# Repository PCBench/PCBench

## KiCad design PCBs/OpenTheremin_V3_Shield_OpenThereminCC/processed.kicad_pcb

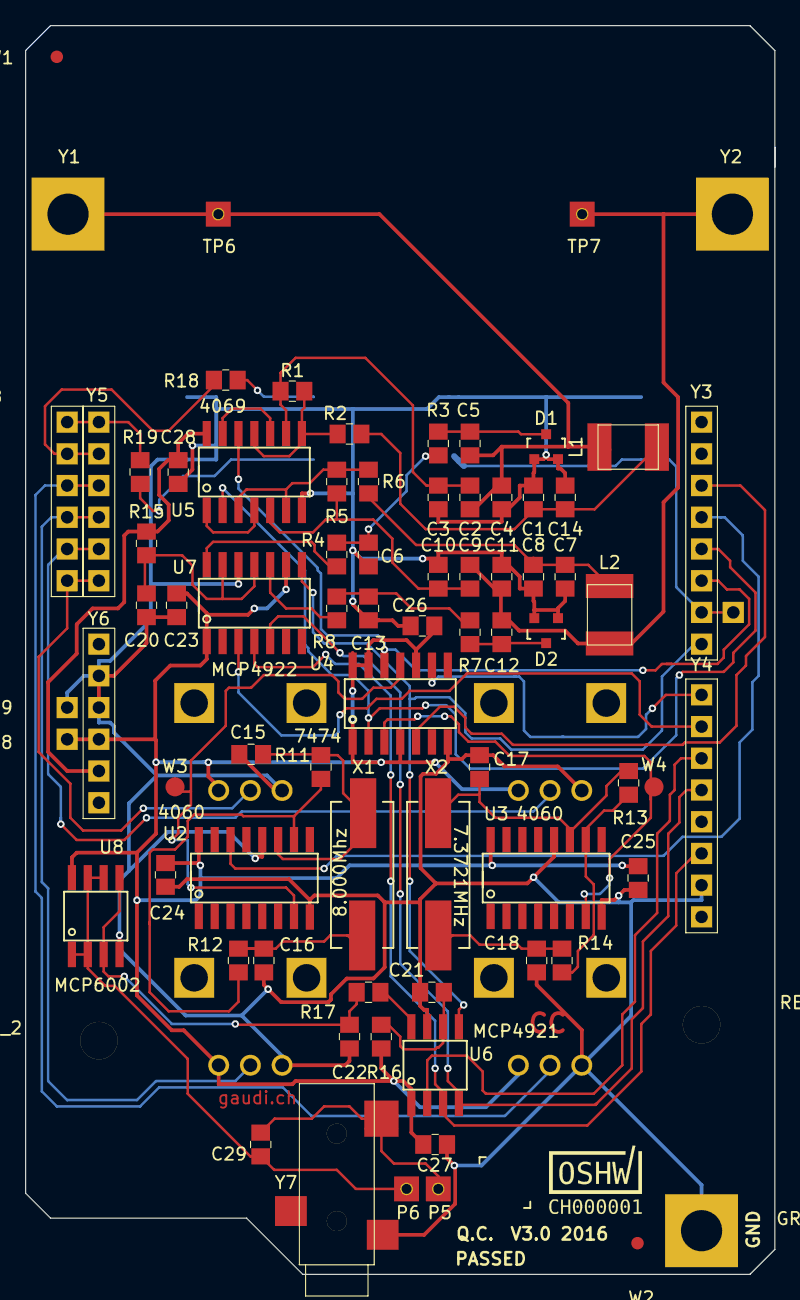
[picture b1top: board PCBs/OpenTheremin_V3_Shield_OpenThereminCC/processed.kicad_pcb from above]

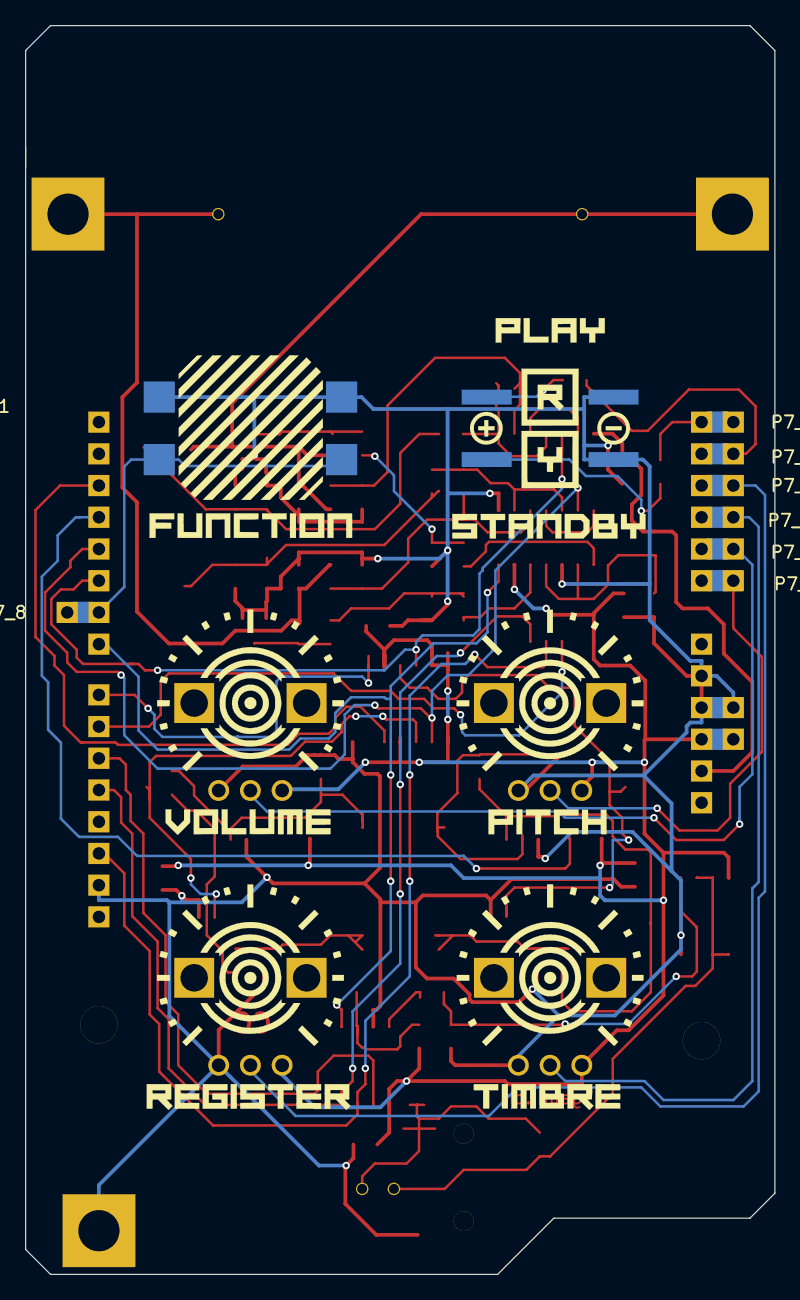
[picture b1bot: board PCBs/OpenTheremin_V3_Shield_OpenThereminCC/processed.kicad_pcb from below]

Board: 2 copper layers, 60.0 x 100.0 mm, 95 parts (17 on the bottom side), 52 nets.

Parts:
C1: 220pF 270pF?; 0805G
C2, C3, C9, C10: 150pF; 0805G
C4: 15nF?; 0805G
C5, C12: 470pF; 0805G
C6, C13, C23, C24, C25, C26, C27, C28: 100nF; 0805G
C7, C14: ?pF; 0805G
C8: 330pF; 0805G
C11: 0; 0805G
C15, C16, C17, C18: 33pF; 0805G
C20, C21: 100n; 0805G
C22: 10n; 0805G
C29: 10uF; 0805G
D1, D2: BB914; SOT-23
D3, D4: LED; LED_SQUARE_5mm
GROUND1: GND_PAD; MountPad3
L1, L2: 1mH; COIL
P1, P2, P3, P4: 10k; POT
P5: SP+; MeasurePad_Square_wHole_2mm
P6: SP-; MeasurePad_Square_wHole_2mm
P7, P7_2, P7_3, P7_4, P7_5, P7_6, P7_7, P7_8, P7_10: CONN_01X01; SMD_Pinheader_1_OT_BLANK
P7_9, P8, P9: CONN_01X01; SMD_Pinheader_1_OT
R1, R5, R11, R13: 4.7M; 0805G
R2, R6, R17: 2.2k; 0805G
R3, R4, R7, R8, R15, R16: 100k; 0805G
R12, R14, R18, R19: 470; 0805G
SW1: SW_PUSH; PUSH_BUTTON_TL3300D
TP6: PITCH ANTENNA; MeasurePad_Square_wHole_2mm
TP7: VOLUME ANTENNA; MeasurePad_Square_wHole_2mm
U1: Arduino_UNO_R2; ArduinoUNO
U2, U3: 4060; SOIC-16_N
U4: 74HC74; SOIC-14_N
U5: 4069; SOIC-14_N
U6: MCP4921-E/SN; SOIC-08_N
U7: MCP4922-E/SL; SOIC-14_N
U8: LM358 / MCP6002; SOIC-08_N
W1: FIDUCIAL1; Fiducial_1mm_Dia_2.54mm_Outer_CopperTop
W2: FIDUCIAL2; Fiducial_1mm_Dia_2.54mm_Outer_CopperTop
W3: TP1; Measurement_Point_Round-SMD-Pad_Small
W4: TP2; Measurement_Point_Round-SMD-Pad_Small
X1: 8MHz; Crystal_HC49-SD_SMD
X2: 7.3721MHz; Crystal_HC49-SD_SMD
Y1, Y2: MountPad3
Y3, Y4: CONN_01X08; SMD_Pinheader_8_OT
Y5, Y6, Y8: CONN_01X06; SMD_Pinheader_6_OT
Y7: PLUG_3_5_SMD; PLUG3_5_SwitchCraft_2B

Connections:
A0: P1.2, Y5.6, Y8.6
A1: P2.2, Y5.5, Y8.5
A2: P3.2, Y5.4, Y8.4
A3: P4.2, Y5.3, Y8.3
BUT: P7_9.1, SW1.1, Y3.7
DAC2_CS: U7.3, Y4.2
DAC_CS: U6.2, Y4.3
DAC_DI: U6.4, U7.5, Y4.4
DAC_LATCH: U6.5, U7.8, Y3.8
DAC_SCK: U6.3, U7.4, Y4.6
F_PITCH: U4.9, Y4.1
F_VOL: U4.5, Y3.3
GND: C1.2, C3.2, C4.2, C6.2, C7.2, C8.2, C10.2, C11.2, C13.2, C14.2, C15.2, C16.2, C17.2, C18.2, C20.2, C21.2, C22.2, C23.2, C24.2, C25.2, C26.2, C27.2, C28.2, D1.1, D1.2, D2.1, D2.2, D3.1, D4.1, GROUND1.1, P1.1, P2.1, P3.1, P4.1, P9.1, SW1.2, U2.8, U2.12, U3.8, U3.12, U4.7, U5.7, U6.7, U7.12, U8.4, Y4.7, Y6.2, Y6.3, Y7.1
LED_GREEN: R18.2, Y5.2, Y8.2
LED_RED: R19.2, Y5.1, Y8.1
unnamed: C1.1, C14.1, L1.2, R2.1
unnamed: C2.1, C4.1, C5.1, L1.1, TP6.1, Y1.1
unnamed: C2.2, C3.1, R1.2, U5.9
unnamed: C5.2, D1.3, R3.2
unnamed: C6.1, R3.1, R4.1
unnamed: C7.1, C8.1, L2.2, R6.1
unnamed: C9.2, C10.1, R5.2, U5.5
unnamed: C9.1, C11.1, C12.1, L2.1, TP7.1, Y2.1
unnamed: C12.2, D2.3, R7.2
unnamed: C13.1, R7.1, R8.1
unnamed: C15.1, R11.2, U2.11, X1.1
unnamed: C16.1, R12.1, X1.2
unnamed: C17.1, R13.2, U3.11, X2.1
unnamed: C18.1, R14.1, X2.2
unnamed: C21.1, R16.1, U6.6
unnamed: C22.1, R17.2, U8.3, U8.5
unnamed: C29.1, P6.1, U8.1, U8.2, U8.6, U8.7
unnamed: C29.2, P5.1, Y7.3
unnamed: D3.2, R18.1
unnamed: D4.2, R19.1
unnamed: R1.1, R2.2, U5.8, U5.11
unnamed: R4.2, U7.14
unnamed: R5.1, R6.2, U5.3, U5.6
unnamed: R11.1, R12.2, U2.10
unnamed: R13.1, R14.2, U3.10
unnamed: R17.1, U6.8
unnamed: U2.7, U4.11, W3.1
unnamed: U3.7, U4.3, W4.1
unnamed: U5.1, U5.4
unnamed: U5.10, U5.13
SAMPLE_CLK: U2.14, Y3.4
VCC: C23.1, C24.1, C25.1, C26.1, C27.1, P1.3, P2.3, P3.3, P4.3, P8.1, R16.2, U2.16, U3.16, U4.1, U4.4, U4.10, U4.13, U4.14, U6.1, U7.1, U7.9, U8.8, Y6.4
VDD: C28.1, R15.2, U5.14, Y6.5
VO_PITCH: U4.12, U5.12, Y3.6
VO_VOL: U4.2, U5.2, Y3.5
VoutB: R8.2, U7.10
VrefB: C20.1, R15.1, U7.11, U7.13

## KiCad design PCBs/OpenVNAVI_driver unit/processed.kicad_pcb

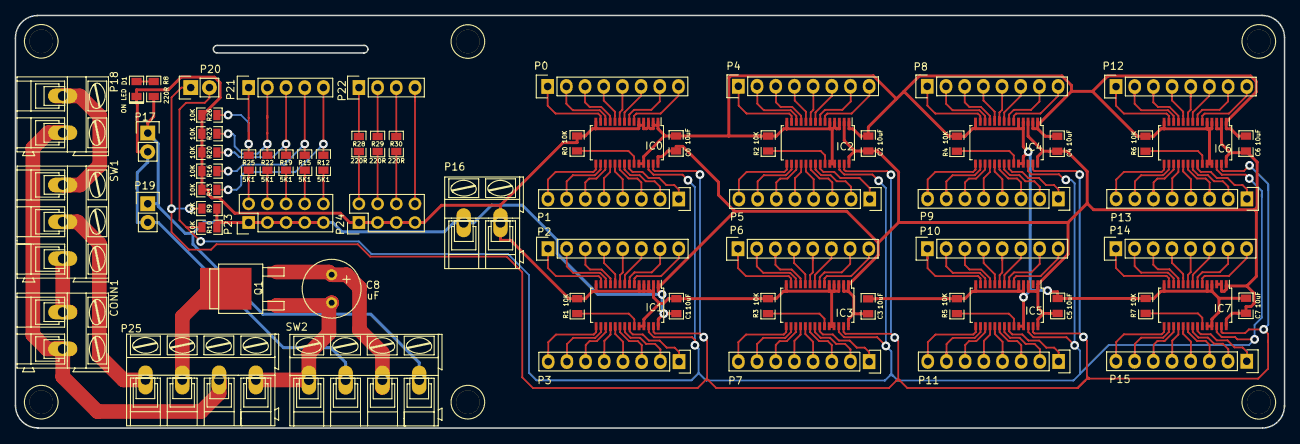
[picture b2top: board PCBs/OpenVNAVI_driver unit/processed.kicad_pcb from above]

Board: 2 copper layers, 172.5 x 56.1 mm, 72 parts (0 on the bottom side), 165 nets.

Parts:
C0, C1, C2, C3, C4, C5, C6, C7: 10uF; SMD0805
C8: uF; Elko_vert_11.5x8mm_RM3.5_CopperClear
CONN1: P. SUP. IN; AK300-2
D1: ON LED; SMD0805_LED
IC0, IC1, IC2, IC3, IC4, IC5, IC6, IC7: PCA9685; TSSOP-28_4.4x9.7mm_Pitch0.65mm
P0, P1, P2, P3, P4, P5, P6, P7, P8, P9, P10, P11, P12, P13, P14, P15: CONN_01X08; Pin_Header_Straight_1x08
P16: PWR Bus; AK300-2
P17: Fan; Pin_Header_Straight_1x02
P18: BATT; AK300-2
P19: RPi2 Power; Pin_Header_Straight_1x02
P20: I2C; Pin_Header_Straight_1x02
P21: GPIO_INPUTS; Pin_Header_Straight_1x05
P22: GPIO_OUTPUTS; Pin_Header_Straight_1x04
P23: GPIO_INPUTS_SWITCHES; Pin_Header_Straight_2x05
P24: GPIO_OUTPUTS_LEDs/SPKR; Pin_Header_Straight_2x04
P25: Buck Converter; AK300-4
Q1: P-MOSFET; TO-252
R0, R1, R2, R3, R4, R5, R6, R7, R9, R10, R13, R16, R20, R23, R26: 10K; SMD0805
R8, R28, R29, R30: 220R; SMD0805
R12, R15, R19, R22, R25: 5K1; SMD0805
SW1: P. SUPPLY/BATT; AK300-3
SW2: ON/OFF; AK300-4

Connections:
+5V: C0.1, C1.1, C2.1, C3.1, C4.1, C5.1, C6.1, C7.1, IC0.28, IC1.1, IC1.28, IC2.2, IC2.28, IC3.1, IC3.2, IC3.28, IC4.3, IC4.28, IC5.1, IC5.3, IC5.28, IC6.2, IC6.3, IC6.28, IC7.1, IC7.2, IC7.3, IC7.28, P16.1, P17.1, P19.1, P23.1, P23.3, P23.5, P23.7, P23.9, R8.1, R9.2, R10.2, SW2.4
/PWM0: IC0.6, P0.8
/PWM1: IC0.7, P0.7
/PWM2: IC0.8, P0.6
/PWM3: IC0.9, P0.5
/PWM4: IC0.10, P0.4
/PWM5: IC0.11, P0.3
/PWM6: IC0.12, P0.2
/PWM7: IC0.13, P0.1
/PWM8: IC0.15, P1.8
/PWM9: IC0.16, P1.7
/PWM10: IC0.17, P1.6
/PWM11: IC0.18, P1.5
/PWM12: IC0.19, P1.4
/PWM13: IC0.20, P1.3
/PWM14: IC0.21, P1.2
/PWM15: IC0.22, P1.1
/PWM16: IC1.6, P2.8
/PWM17: IC1.7, P2.7
/PWM18: IC1.8, P2.6
/PWM19: IC1.9, P2.5
/PWM20: IC1.10, P2.4
/PWM21: IC1.11, P2.3
/PWM22: IC1.12, P2.2
/PWM23: IC1.13, P2.1
/PWM24: IC1.15, P3.8
/PWM25: IC1.16, P3.7
/PWM26: IC1.17, P3.6
/PWM27: IC1.18, P3.5
/PWM28: IC1.19, P3.4
/PWM29: IC1.20, P3.3
/PWM30: IC1.21, P3.2
/PWM31: IC1.22, P3.1
/PWM32: IC2.6, P4.8
/PWM33: IC2.7, P4.7
/PWM34: IC2.8, P4.6
/PWM35: IC2.9, P4.5
/PWM36: IC2.10, P4.4
/PWM37: IC2.11, P4.3
/PWM38: IC2.12, P4.2
/PWM39: IC2.13, P4.1
/PWM40: IC2.15, P5.8
/PWM41: IC2.16, P5.7
/PWM42: IC2.17, P5.6
/PWM43: IC2.18, P5.5
/PWM44: IC2.19, P5.4
/PWM45: IC2.20, P5.3
/PWM46: IC2.21, P5.2
/PWM47: IC2.22, P5.1
/PWM48: IC3.6, P6.8
/PWM49: IC3.7, P6.7
/PWM50: IC3.8, P6.6
/PWM51: IC3.9, P6.5
/PWM52: IC3.10, P6.4
/PWM53: IC3.11, P6.3
/PWM54: IC3.12, P6.2
/PWM55: IC3.13, P6.1
/PWM56: IC3.15, P7.8
/PWM57: IC3.16, P7.7
/PWM58: IC3.17, P7.6
/PWM59: IC3.18, P7.5
/PWM60: IC3.19, P7.4
/PWM61: IC3.20, P7.3
/PWM62: IC3.21, P7.2
/PWM63: IC3.22, P7.1
/PWM64: IC4.6, P8.8
/PWM65: IC4.7, P8.7
/PWM66: IC4.8, P8.6
/PWM67: IC4.9, P8.5
/PWM68: IC4.10, P8.4
/PWM69: IC4.11, P8.3
/PWM70: IC4.12, P8.2
/PWM71: IC4.13, P8.1
/PWM72: IC4.15, P9.8
/PWM73: IC4.16, P9.7
/PWM74: IC4.17, P9.6
/PWM75: IC4.18, P9.5
/PWM76: IC4.19, P9.4
/PWM77: IC4.20, P9.3
/PWM78: IC4.21, P9.2
/PWM79: IC4.22, P9.1
/PWM80: IC5.6, P10.8
/PWM81: IC5.7, P10.7
/PWM82: IC5.8, P10.6
/PWM83: IC5.9, P10.5
/PWM84: IC5.10, P10.4
/PWM85: IC5.11, P10.3
/PWM86: IC5.12, P10.2
/PWM87: IC5.13, P10.1
/PWM88: IC5.15, P11.8
/PWM89: IC5.16, P11.7
/PWM90: IC5.17, P11.6
/PWM91: IC5.18, P11.5
/PWM92: IC5.19, P11.4
/PWM93: IC5.20, P11.3
/PWM94: IC5.21, P11.2
/PWM95: IC5.22, P11.1
/PWM96: IC6.6, P12.8
/PWM97: IC6.7, P12.7
/PWM98: IC6.8, P12.6
/PWM99: IC6.9, P12.5
/PWM100: IC6.10, P12.4
/PWM101: IC6.11, P12.3
/PWM102: IC6.12, P12.2
/PWM103: IC6.13, P12.1
/PWM104: IC6.15, P13.8
/PWM105: IC6.16, P13.7
/PWM106: IC6.17, P13.6
/PWM107: IC6.18, P13.5
/PWM108: IC6.19, P13.4
/PWM109: IC6.20, P13.3
/PWM110: IC6.21, P13.2
/PWM111: IC6.22, P13.1
/PWM112: IC7.6, P14.8
/PWM113: IC7.7, P14.7
/PWM114: IC7.8, P14.6
/PWM115: IC7.9, P14.5
/PWM116: IC7.10, P14.4
/PWM117: IC7.11, P14.3
/PWM118: IC7.12, P14.2
/PWM119: IC7.13, P14.1
/PWM120: IC7.15, P15.8
/PWM121: IC7.16, P15.7
/PWM122: IC7.17, P15.6
/PWM123: IC7.18, P15.5
/PWM124: IC7.19, P15.4
/PWM125: IC7.20, P15.3
/PWM126: IC7.21, P15.2
/PWM127: IC7.22, P15.1
/SCL: IC0.26, IC1.26, IC2.26, IC3.26, IC4.26, IC5.26, IC6.26, IC7.26, P20.2, R10.1
/SDA: IC0.27, IC1.27, IC2.27, IC3.27, IC4.27, IC5.27, IC6.27, IC7.27, P20.1, R9.1
GND: C0.2, C1.2, C2.2, C3.2, C4.2, C5.2, C6.2, C7.2, D1.1, IC0.1, IC0.2, IC0.3, IC0.4, IC0.5, IC0.14, IC0.24, IC0.25, IC1.2, IC1.3, IC1.4, IC1.5, IC1.14, IC1.24, IC1.25, IC2.1, IC2.3, IC2.4, IC2.5, IC2.14, IC2.24, IC2.25, IC3.3, IC3.4, IC3.5, IC3.14, IC3.24, IC3.25, IC4.1, IC4.2, IC4.4, IC4.5, IC4.14, IC4.24, IC4.25, IC5.4, IC5.5, IC5.14, IC5.24, IC5.25, IC6.1, IC6.4, IC6.5, IC6.14, IC6.24, IC6.25, IC7.4, IC7.5, IC7.14, IC7.24, IC7.25, P16.2, P17.2, P19.2, P24.1, P24.3, P24.5, P24.7, R0.2, R1.2, R2.2, R3.2, R4.2, R5.2, R6.2, R7.2, R13.2, R16.2, R20.2, R23.2, R26.2, SW2.2
unnamed: C8.1, Q1.3, SW2.3
unnamed: C8.2, P25.4, Q1.2, SW2.1
unnamed: CONN1.1, SW1.3
unnamed: CONN1.2, P18.2, P25.3
unnamed: D1.2, R8.2
unnamed: IC0.23, R0.1
unnamed: IC1.23, R1.1
unnamed: IC2.23, R2.1
unnamed: IC3.23, R3.1
unnamed: IC4.23, R4.1
unnamed: IC5.23, R5.1
unnamed: IC6.23, R6.1
unnamed: IC7.23, R7.1
unnamed: P18.1, SW1.1
unnamed: P21.1, R25.2, R26.1
unnamed: P21.2, R22.2, R23.1
unnamed: P21.3, R19.2, R20.1
unnamed: P21.4, R15.2, R16.1
unnamed: P21.5, R12.2, R13.1
unnamed: P22.1, R28.1
unnamed: P22.2, R29.1
unnamed: P22.3, R30.1
unnamed: P22.4, P24.8
unnamed: P23.2, R25.1
unnamed: P23.4, R22.1
unnamed: P23.6, R19.1
unnamed: P23.8, R15.1
unnamed: P23.10, R12.1
unnamed: P24.2, R28.2
unnamed: P24.4, R29.2
unnamed: P24.6, R30.2
unnamed: P25.1, SW1.2
unnamed: P25.2, Q1.1

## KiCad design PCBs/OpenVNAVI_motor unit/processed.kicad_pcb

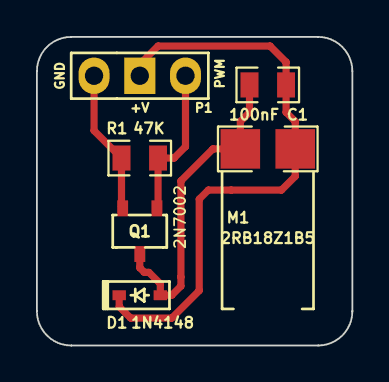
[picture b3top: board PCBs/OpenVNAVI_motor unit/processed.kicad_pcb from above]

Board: 2 copper layers, 17.5 x 17.1 mm, 6 parts (0 on the bottom side), 4 nets.

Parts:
C1: 100nF; SMD0805
D1: 1N4148; SOD-323
M1: 2RB18Z1B5; Vibration_motor
P1: CONN; Pin_Header_Straight_1x03_MOD
Q1: 2N7002; SOT23-5_MOD_PINOUT
R1: 47K; SMD0805

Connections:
+5V: C1.1, D1.1, M1.1, P1.2
GND: P1.1, Q1.3, R1.2
unnamed: C1.2, D1.2, M1.2, Q1.1
unnamed: P1.3, Q1.2, R1.1

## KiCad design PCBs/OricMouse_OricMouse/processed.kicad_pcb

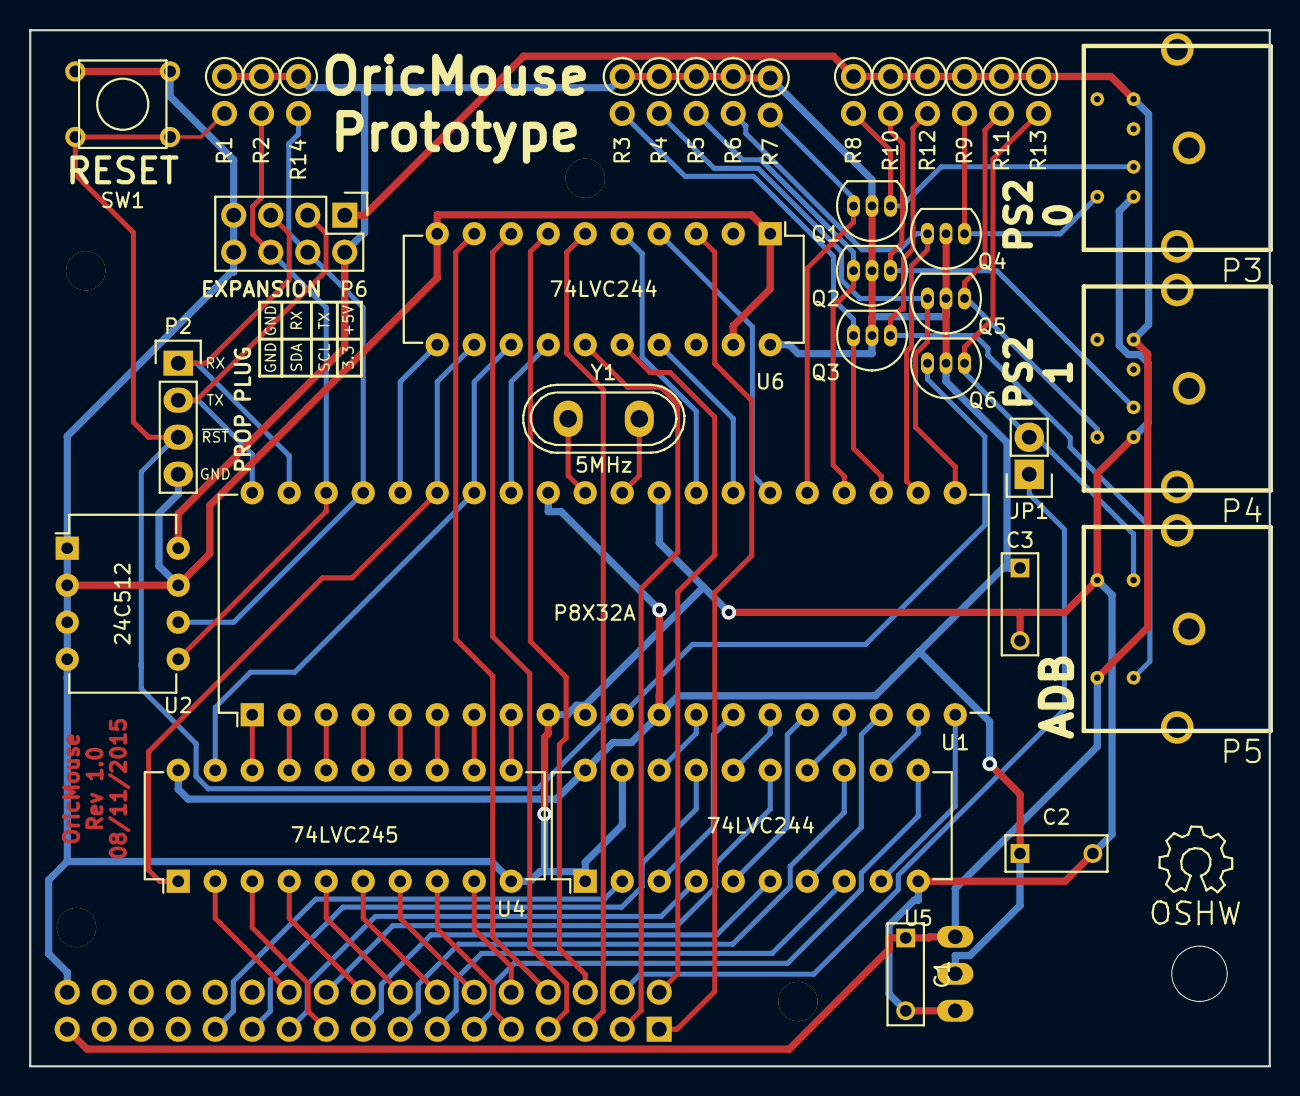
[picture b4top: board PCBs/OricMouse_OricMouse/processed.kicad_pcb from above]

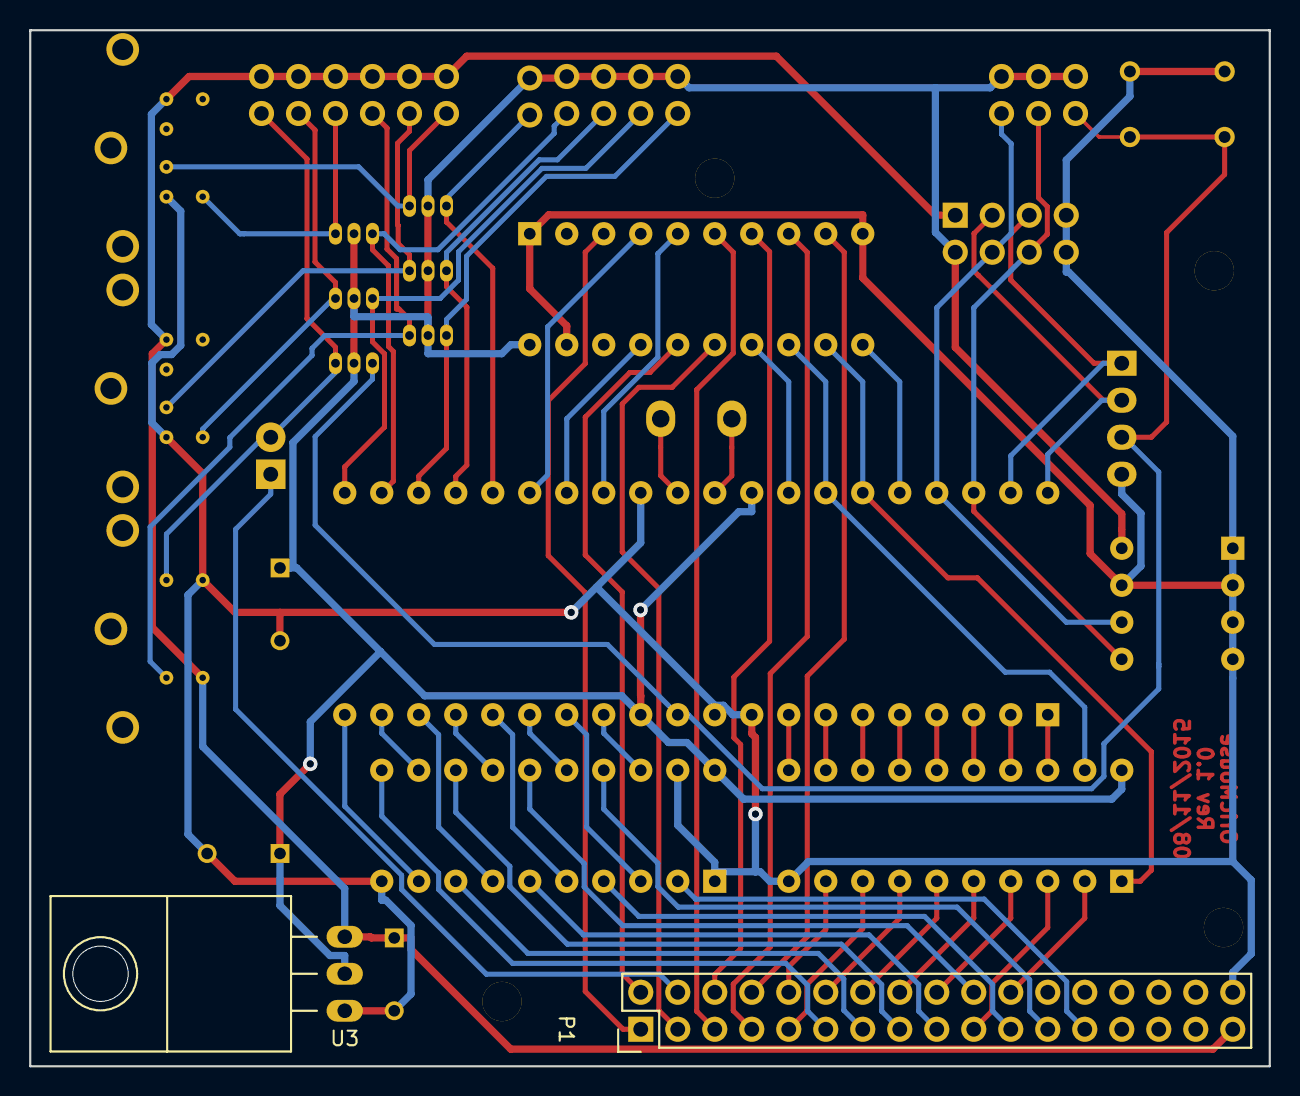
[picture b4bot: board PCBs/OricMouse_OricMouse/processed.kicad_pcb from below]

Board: 2 copper layers, 85.1 x 71.1 mm, 43 parts (2 on the bottom side), 68 nets.

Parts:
C1, C2: 0.1uF; C_Rect_L7_W2.5_P5
C3: 1uF; C_Rect_L7_W2.5_P5
Hole1, Hole2, Hole3, Hole4: MountingHole_2-7mm
JP1: JUMPER; Pin_Header_Straight_1x02
OSHW: Symbol_OSHW-Logo_SilkScreen
P1: CONN_02X17; Pin_Header_Straight_2x17
P2: PROP PLUG; Pin_Header_Straight_1x04
P3: PS2/0; MiniDIN6
P4: PS2 / 1; MiniDIN6
P5: ADB; MiniDIN4
P6: EXPANSION; Pin_Header_Straight_2x04
Q1, Q2, Q3, Q4, Q5, Q6: BS170; TO-92_Inline_Narrow_Oval
R1, R2, R3, R4, R5, R6, R7, R8, R9, R10, R11, R12, R13, R14: 10K; Resistor_Vertical_RM5mm
SW1: RESET; SW_PUSH_SMALL
U1: P8X32A; DIP-40_W15.24mm
U2: 24C512; DIP-8_W7.62mm
U3: LD1117; TO-220_Neutral123_Horizontal
U4: 74LVC245; DIP-20_W7.62mm
U5, U6: 74LVC244; DIP-20_W7.62mm
Y1: 5MHz; Crystal_HC50-U_Vertical

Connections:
+3V3: C2.1, C3.1, P6.2, Q1.2, Q2.2, Q3.2, Q4.2, Q5.2, Q6.2, R1.1, R2.1, R3.1, R4.1, R5.1, R6.1, R7.1, R14.1, U1.12, U1.32, U2.8, U3.2, U4.20, U5.20, U6.20
+5V: C1.1, P1.33, P3.4, P4.4, P5.3, P6.1, R8.1, R9.1, R10.1, R11.1, R12.1, R13.1, U3.3
/A0: P1.13, U5.8
/A1: P1.15, U5.13
/A2: P1.17, U5.6
/A3: P1.11, U5.11
/A4: P1.20, U5.15
/A5: P1.21, U5.4
/A6: P1.23, U5.17
/A7: P1.25, U5.2
/ADB_DATA: Q3.3, R3.2, U1.23
/D0: P1.10, U4.9
/D1: P1.12, U4.7
/D2: P1.9, U4.8
/D3: P1.16, U4.5
/D4: P1.18, U4.4
/D5: P1.19, U4.3
/D6: P1.14, U4.6
/D7: P1.22, U4.2
/I/O: P1.5, U6.6
/I/O_C: P1.6, U6.7
/PS2_0_CLK: Q4.3, R6.2, U1.22
/PS2_0_DATA: Q1.3, R7.2, U1.25
/PS2_1_CLK: Q5.3, R4.2, U1.21
/PS2_1_DATA: Q2.3, R5.2, U1.24
/Phi2: P1.3, U6.15
/R/W: P1.7, U6.8
/RX: P2.1, P6.5, U1.39
/SCL: P6.4, R14.2, U1.37, U2.6
/SDA: P6.6, R2.2, U1.38, U2.5
/TX: P2.2, P6.3, U1.40
/mA0: U1.19, U5.12
/mA1: U1.18, U5.7
/mA2: U1.17, U5.14
/mA3: U1.20, U5.9
/mA4: U1.16, U5.5
/mA5: U1.15, U5.16
/mA6: U1.14, U5.3
/mA7: U1.13, U5.18
/mD0: U1.8, U4.11
/mD1: U1.6, U4.13
/mD2: U1.7, U4.12
/mD3: U1.4, U4.15
/mD4: U1.3, U4.16
/mD5: U1.2, U4.17
/mD6: U1.5, U4.14
/mD7: U1.1, U4.18
/mIO: U1.33, U6.14
/mIOc: U1.34, U4.19, U6.13
/mIRQ: U1.36, U6.11
/mMAP: U1.27, U6.17
/mPhi2: U1.28, U6.5
/mROMDIS: U1.26, U6.4
/mRW: U1.35, U4.1, U6.12
/~IRQ: P1.8, U6.9
/~MAP: P1.1, U6.3
/~RESET: JP1.2, P5.2, Q6.1, R13.2
/~ROMDIS: P1.2, U6.16
/~RST: P2.3, Q6.3, R1.2, SW1.2, U1.11
GND: C1.2, C2.2, C3.2, P1.34, P2.4, P3.3, P4.3, P5.4, P6.7, P6.8, SW1.1, U1.9, U1.10, U1.29, U2.1, U2.2, U2.3, U2.4, U2.7, U3.1, U4.10, U5.1, U5.10, U5.19, U6.1, U6.10, U6.19
unnamed: JP1.1, P1.4
unnamed: P3.1, Q1.1, R8.2
unnamed: P3.5, Q4.1, R9.2
unnamed: P4.1, Q2.1, R10.2
unnamed: P4.5, Q5.1, R11.2
unnamed: P5.1, Q3.1, R12.2
unnamed: U1.30, Y1.2
unnamed: U1.31, Y1.1

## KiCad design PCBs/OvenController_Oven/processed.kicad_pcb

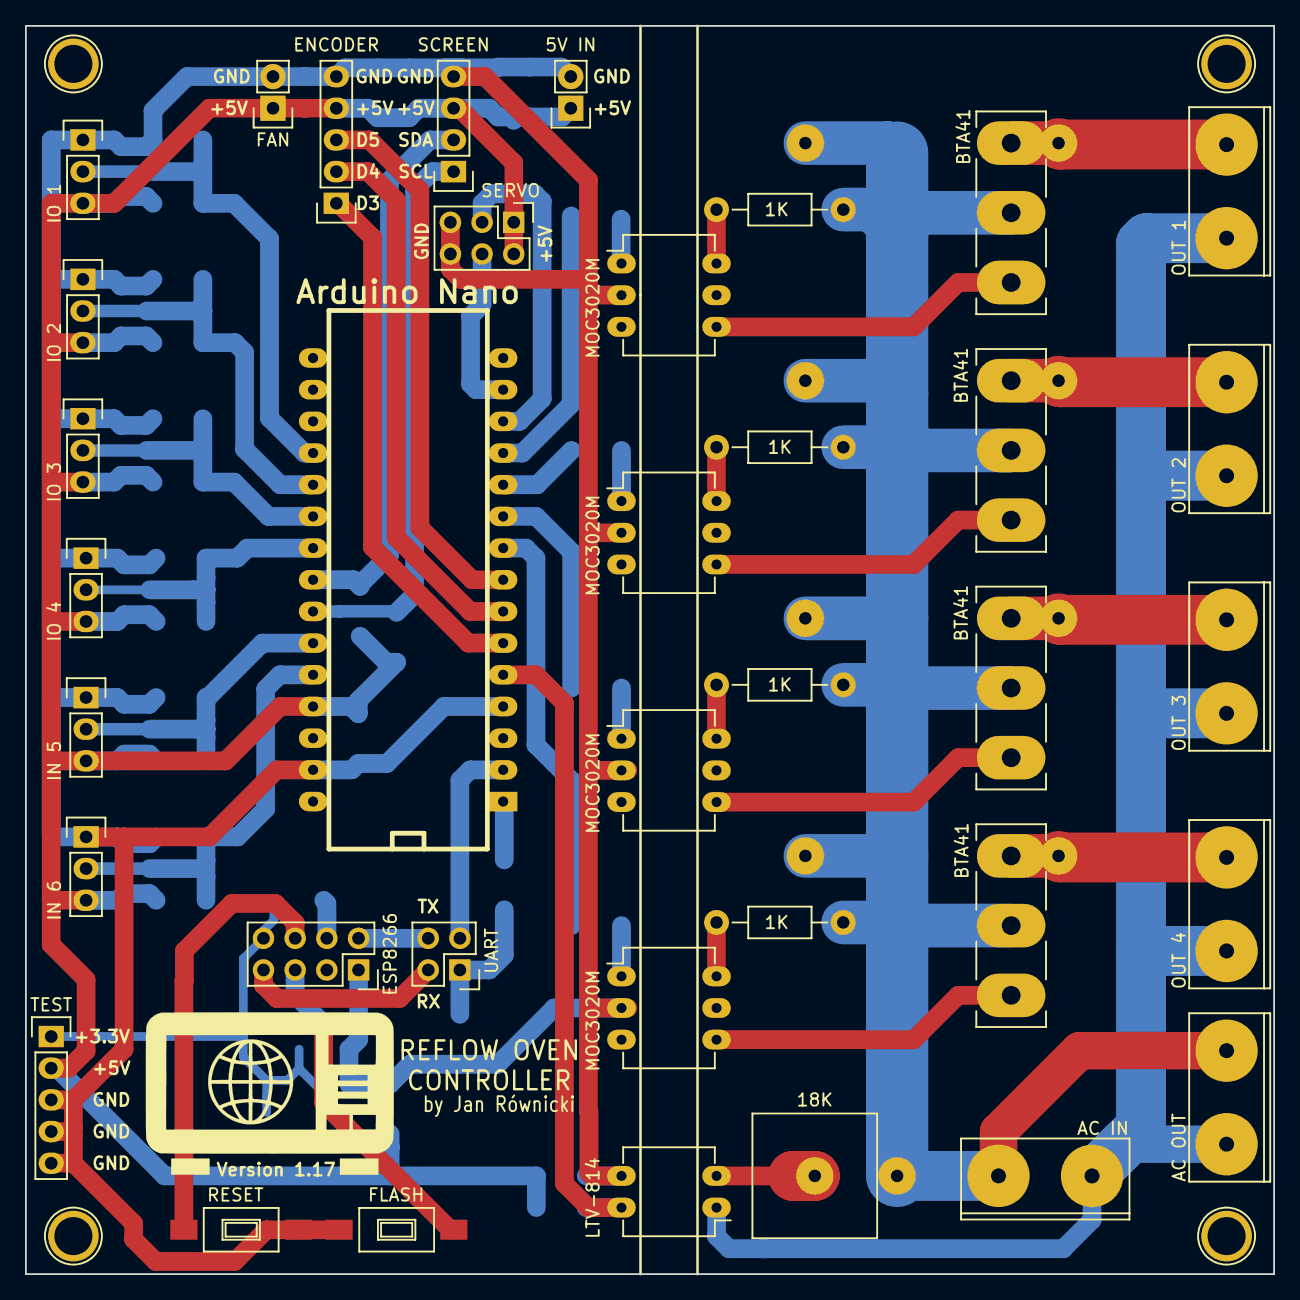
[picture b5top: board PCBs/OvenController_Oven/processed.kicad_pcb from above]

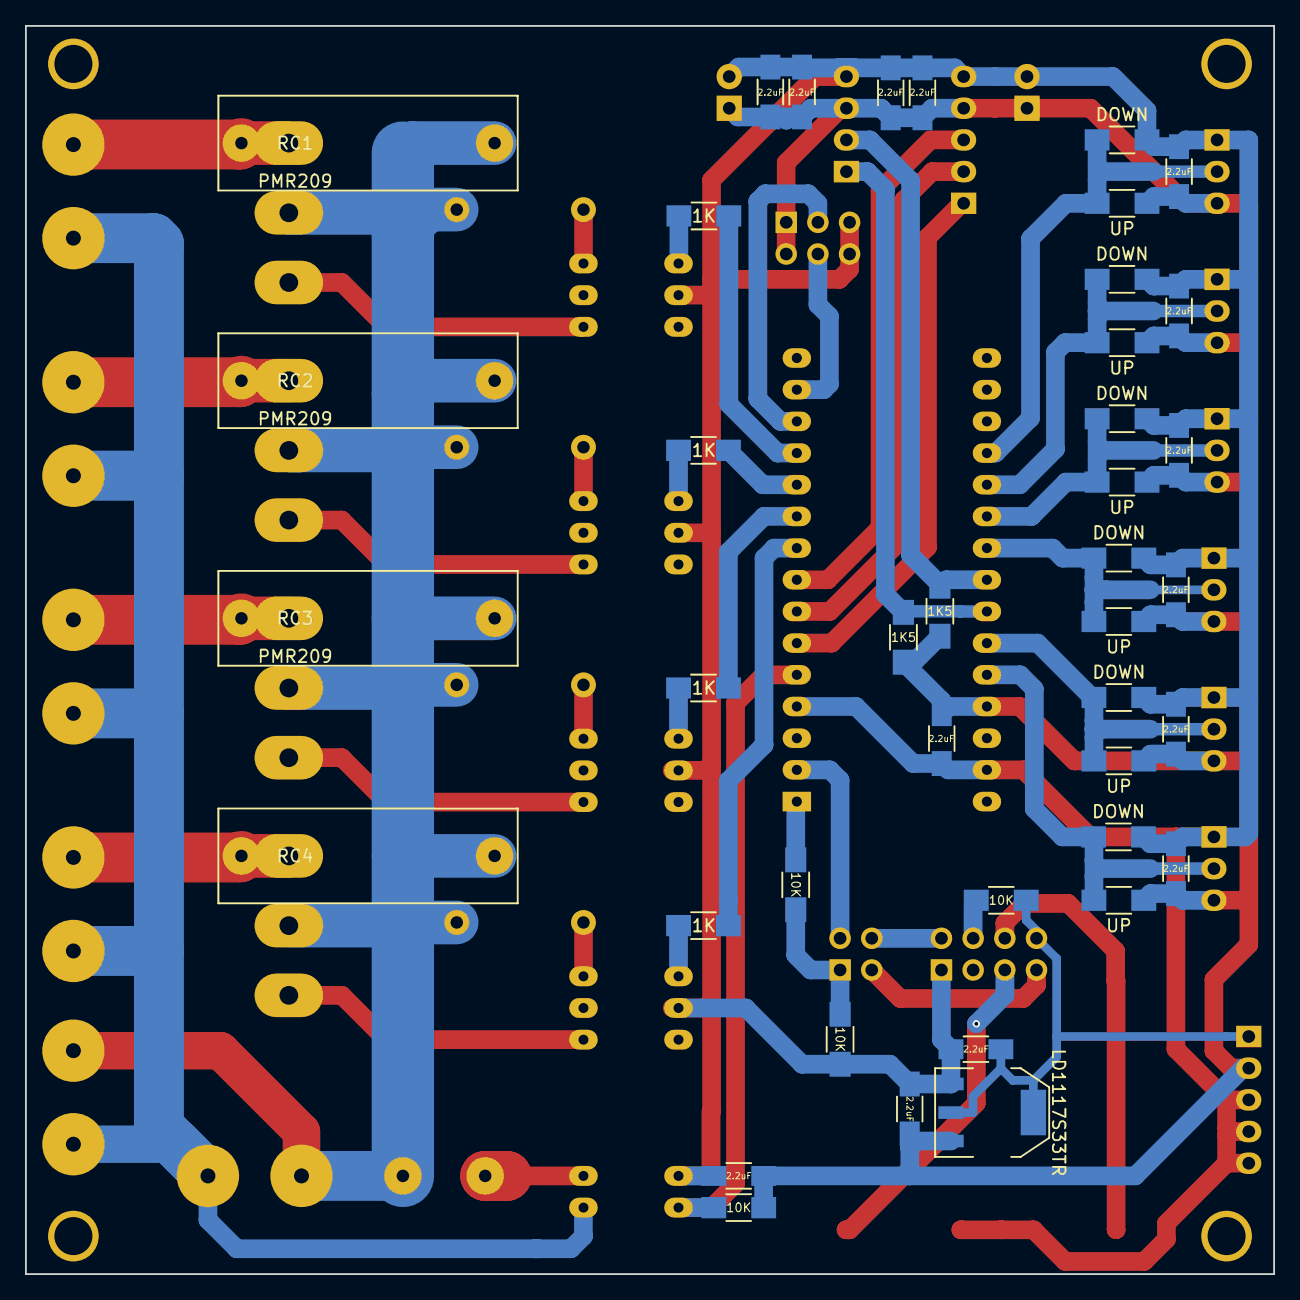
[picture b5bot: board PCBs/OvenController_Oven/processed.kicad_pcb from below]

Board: 2 copper layers, 100.1 x 100.1 mm, 82 parts (41 on the bottom side), 48 nets.

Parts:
C1, C2, C3, C4, C5, C6, C7, C8, C9, C10, C11, C12, C13, C14: 2.2uF; C_1206_HandSoldering
P1: IO 1; Pin_Header_Straight_1x03
P2: OUT 1; TerminalBlock_7.5mm_2pol
P3: IO 2; Pin_Header_Straight_1x03
P4: OUT 2; TerminalBlock_7.5mm_2pol
P5: IO 3; Pin_Header_Straight_1x03
P6: IO 4; Pin_Header_Straight_1x03
P7: ENCODER; Pin_Header_Straight_1x05
P8: OUT 3; TerminalBlock_7.5mm_2pol
P9: SCREEN; Pin_Header_Straight_1x04
P10: IN 5; Pin_Header_Straight_1x03
P11: OUT 4; TerminalBlock_7.5mm_2pol
P12: IN 6; Pin_Header_Straight_1x03
P13: AC IN; TerminalBlock_7.5mm_2pol
P14: ESP8266; Socket_Strip_Straight_2x04
P15, P16, P17, P18: MOUNT; 1pin
P19: 5V IN; Pin_Header_Straight_1x02
P20: AC OUT; TerminalBlock_7.5mm_2pol
P21: TEST; Pin_Header_Straight_1x05
P22: UART; Pin_Header_Straight_2x02
P23: SERVO; Pin_Header_Straight_2x03
P24: FAN; Pin_Header_Straight_1x02
R1, R7, R11, R17: 1K; Resistor_Horizontal_RM10mm
R2, R5, R9, R18, R22, R24: UP; R_1206_HandSoldering
R3, R6, R10, R20, R23, R25: DOWN; R_1206_HandSoldering
R4, R8, R14, R21: 1K; R_1206_HandSoldering
R12, R13, R15, R16: 10K; R_1206_HandSoldering
R19: 18K; VerticalResistor
R26, R27: 1K5; R_1206_HandSoldering
RC1, RC2, RC3, RC4: PMR209; RC
SW1: RESET; SW_SPST_FSMSM
SW2: FLASH; SW_SPST_FSMSM
U1, U3, U6, U9: BTA41; TO-247_Vertical_Neutral123_largePads
U2, U4, U7, U10: MOC3020M; DIP-6_W7.62mm_LongPads
U5: Arduino Nano; arduino_mini
U8: LTV-814; DIP-4_W7.62mm_LongPads
U11: LD1117S33TR; SOT-223

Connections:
+3V3: C12.1, P14.8, P21.1, R13.1, U11.2, U11.4
+5V: C1.1, C2.1, C3.1, C4.1, C5.1, C6.1, C7.1, C8.1, C9.1, C10.1, C11.1, C13.1, C14.1, P1.3, P3.3, P5.3, P6.3, P7.4, P9.3, P10.3, P12.3, P19.1, P21.2, P23.1, P23.2, P24.1, R2.2, R5.2, R9.2, R15.2, R18.2, R22.2, R24.2, R26.2, R27.2, U5.27, U11.3
/CH1: R4.2, U5.12
/CH2: R8.2, U5.11
/CH3: R14.2, U5.10
/CH4: R21.2, U5.9
/ESP_RXD: P14.7, P22.2
/ESP_TXD: P14.2, P22.4
/IN5: P10.2, R22.1, R23.2, U5.25
/IN6: P12.2, R24.1, R25.2, U5.26
/IO1: P1.2, R2.1, R3.2, U5.19
/IO2: P3.2, R5.1, R6.2, U5.20
/IO3: P5.2, R9.1, R10.2, U5.21
/IO4: P6.2, R18.1, R20.2, U5.22
/PWR+: P13.1, P20.2, R1.1, R7.1, R11.1, R17.1, R19.2, RC1.1, RC2.1, RC3.1, RC4.1, U1.2, U3.2, U6.2, U9.2
/PWR-: P2.1, P4.1, P8.1, P11.1, P13.2, P20.1, U8.1
GND: C1.2, C2.2, C3.2, C4.2, C5.2, C6.2, C7.2, C8.2, C9.2, C10.2, C11.2, C12.2, C13.2, C14.2, P1.1, P3.1, P5.1, P6.1, P7.5, P9.4, P10.1, P12.1, P14.1, P19.2, P21.3, P21.4, P21.5, P23.5, P23.6, P24.2, R3.1, R6.1, R10.1, R16.1, R20.1, R23.1, R25.1, SW1.1, SW2.1, U2.2, U4.2, U5.4, U5.29, U7.2, U8.3, U10.2, U11.1
unnamed: P2.2, RC1.2, U1.1
unnamed: P4.2, RC2.2, U3.1
unnamed: P7.1, U5.6
unnamed: P7.2, U5.7
unnamed: P7.3, U5.8
unnamed: P8.2, RC3.2, U6.1
unnamed: P9.1, R27.1, U5.24
unnamed: P9.2, R26.1, U5.23
unnamed: P11.2, RC4.2, U9.1
unnamed: P14.4, R13.2
unnamed: P14.5, SW2.2
unnamed: P14.6, SW1.2
unnamed: P22.1, R12.1, R16.2
unnamed: P22.3, U5.2
unnamed: P23.3, U5.13
unnamed: P23.4, U5.14
unnamed: R1.2, U2.6
unnamed: R4.1, U2.1
unnamed: R7.2, U4.6
unnamed: R8.1, U4.1
unnamed: R11.2, U7.6
unnamed: R12.2, U5.1
unnamed: R14.1, U7.1
unnamed: R15.1, U5.5, U8.4
unnamed: R17.2, U10.6
unnamed: R19.1, U8.2
unnamed: R21.1, U10.1
unnamed: U1.3, U2.4
unnamed: U3.3, U4.4
unnamed: U6.3, U7.4
unnamed: U9.3, U10.4
